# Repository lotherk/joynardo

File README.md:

# Joynardo

DIY joystick built with an [Arduino Leonardo](http://arduino.cc/en/pmwiki.php?n=Main/arduinoBoardLeonardo).

It uses the patches from [this](http://www.imaginaryindustries.com/blog/?p=80) website to turn the Leonardo into a USB HID Joystick.

The code will basically work on (most) other Arduinos except for the actual [Joystick Implementation](src/JoystickImpl.cpp).

It is shared with the public for research and learning purposes.

## Build

The project is created using [ino](http://inotool.org/). See the [ino.ini](ino.ini) file for configuration options.

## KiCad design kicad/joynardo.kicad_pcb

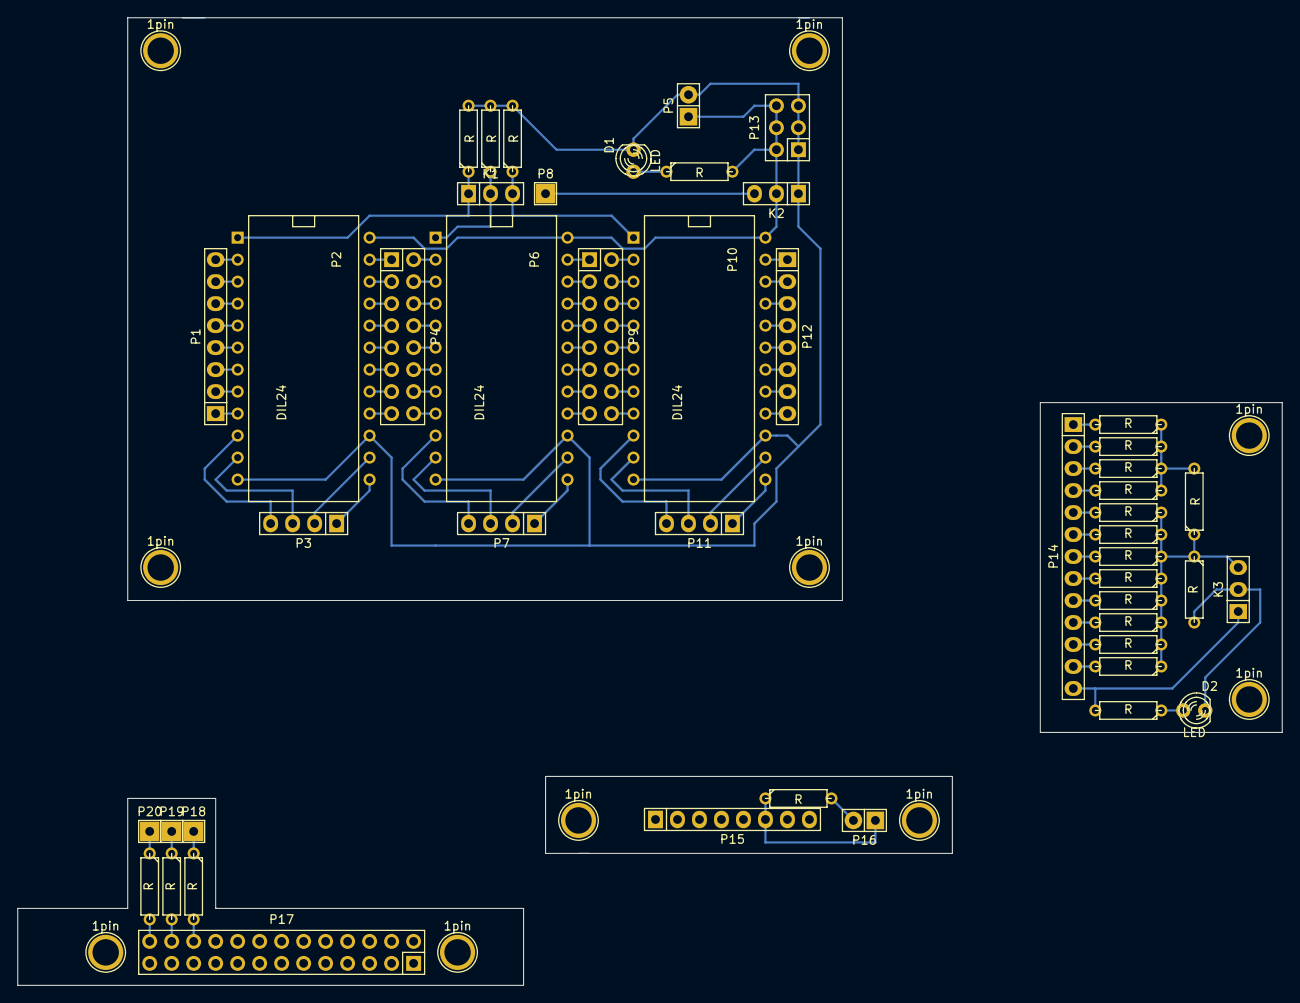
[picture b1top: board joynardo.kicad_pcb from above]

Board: 2 copper layers, 146.1 x 111.8 mm, 58 parts (0 on the bottom side), 92 nets.

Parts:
1pin, 1pin#2, 1pin#3, 1pin#4, 1pin#5, 1pin#6, 1pin#7, 1pin#8, 1pin#9, 1pin#10: VAL**; 1pin
D1, D2: LED; LED-3MM
K1: MUX; Pin_Header_Straight_1x03
K2, K3: CONN_3; Pin_Header_Straight_1x03
P1, P12: CONN_8; Pin_Header_Straight_1x08
P2, P6, P10: DIL24; DIP-24__600
P3, P7, P11: CONN_4; Pin_Header_Straight_1x04
P4, P9: CONN_8X2; Pin_Header_Straight_2x08
P5: +5v -; Pin_Header_Straight_1x02
P8, P18, P19, P20: CONN_1; Pin_Header_Straight_1x01
P13: CONN_02X03; Pin_Header_Straight_2x03
P14: CONN_01X13; Socket_Strip_Straight_1x13
P15: CONN_8; Socket_Strip_Straight_1x08
P16: CONN_2; Pin_Header_Straight_1x02
P17: CONN_02X13; Socket_Strip_Straight_2x13
R1, R2, R3, R4, R5, R6, R7, R8, R9, R10, R11, R12, R13, R14, R15, R16, R17, R18, R19, R20, R21, R22, R23: R; R3

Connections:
unnamed: D1.1, R4.1
unnamed: D1.2, K2.1, P2.12, P2.15, P5.2, P6.12, P6.15, P10.12, P10.15, P13.1, P13.3, P13.5, R1.2, R2.2, R3.2
unnamed: D2.1, R19.1
unnamed: D2.2, K3.2, R18.2
unnamed: K1.1, P2.1, R1.1
unnamed: K1.2, P6.1, R2.1
unnamed: K1.3, P10.1, R3.1
unnamed: K2.2, P2.24, P5.1, P6.24, P10.24, P13.2, P13.4, P13.6, R4.2
unnamed: K2.3, P8.1
unnamed: K3.1, P14.13, R19.2
unnamed: K3.3, R5.1, R6.1, R7.1, R8.1, R9.1, R10.1, R11.1, R12.1, R17.1, R18.1
unnamed: P1.1, P2.9
unnamed: P1.2, P2.8
unnamed: P1.3, P2.7
unnamed: P1.4, P2.6
unnamed: P1.5, P2.5
unnamed: P1.6, P2.4
unnamed: P1.7, P2.3
unnamed: P1.8, P2.2
unnamed: P2.10, P3.4
unnamed: P2.11, P3.3
unnamed: P2.13, P3.1
unnamed: P2.14, P3.2
unnamed: P2.16, P4.15
unnamed: P2.17, P4.13
unnamed: P2.18, P4.11
unnamed: P2.19, P4.9
unnamed: P2.20, P4.7
unnamed: P2.21, P4.5
unnamed: P2.22, P4.3
unnamed: P2.23, P4.1
unnamed: P4.2, P6.2
unnamed: P4.4, P6.3
unnamed: P4.6, P6.4
unnamed: P4.8, P6.5
unnamed: P4.10, P6.6
unnamed: P4.12, P6.7
unnamed: P4.14, P6.8
unnamed: P4.16, P6.9
unnamed: P6.10, P7.4
unnamed: P6.11, P7.3
unnamed: P6.13, P7.1
unnamed: P6.14, P7.2
unnamed: P6.16, P9.15
unnamed: P6.17, P9.13
unnamed: P6.18, P9.11
unnamed: P6.19, P9.9
unnamed: P6.20, P9.7
unnamed: P6.21, P9.5
unnamed: P6.22, P9.3
unnamed: P6.23, P9.1
unnamed: P9.2, P10.2
unnamed: P9.4, P10.3
unnamed: P9.6, P10.4
unnamed: P9.8, P10.5
unnamed: P9.10, P10.6
unnamed: P9.12, P10.7
unnamed: P9.14, P10.8
unnamed: P9.16, P10.9
unnamed: P10.10, P11.4
unnamed: P10.11, P11.3
unnamed: P10.13, P11.1
unnamed: P10.14, P11.2
unnamed: P10.16, P12.8
unnamed: P10.17, P12.7
unnamed: P10.18, P12.6
unnamed: P10.19, P12.5
unnamed: P10.20, P12.4
unnamed: P10.21, P12.3
unnamed: P10.22, P12.2
unnamed: P10.23, P12.1
unnamed: P14.1, R16.2
unnamed: P14.2, R15.2
unnamed: P14.3, R14.2
unnamed: P14.4, R13.2
unnamed: P14.5, R12.2
unnamed: P14.6, R11.2
unnamed: P14.7, R10.2
unnamed: P14.8, R9.2
unnamed: P14.9, R8.2
unnamed: P14.10, R7.2
unnamed: P14.11, R6.2
unnamed: P14.12, R5.2
unnamed: P15.6, P16.1, R20.1
unnamed: P16.2, R20.2
unnamed: P17.22, R21.2
unnamed: P17.24, R22.2
unnamed: P17.26, R23.2
unnamed: P18.1, R21.1
unnamed: P19.1, R22.1
unnamed: P20.1, R23.1
unnamed: R13.1, R14.1, R15.1, R16.1, R17.2

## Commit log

2015-02-25 initial import
2015-02-25 relocate
